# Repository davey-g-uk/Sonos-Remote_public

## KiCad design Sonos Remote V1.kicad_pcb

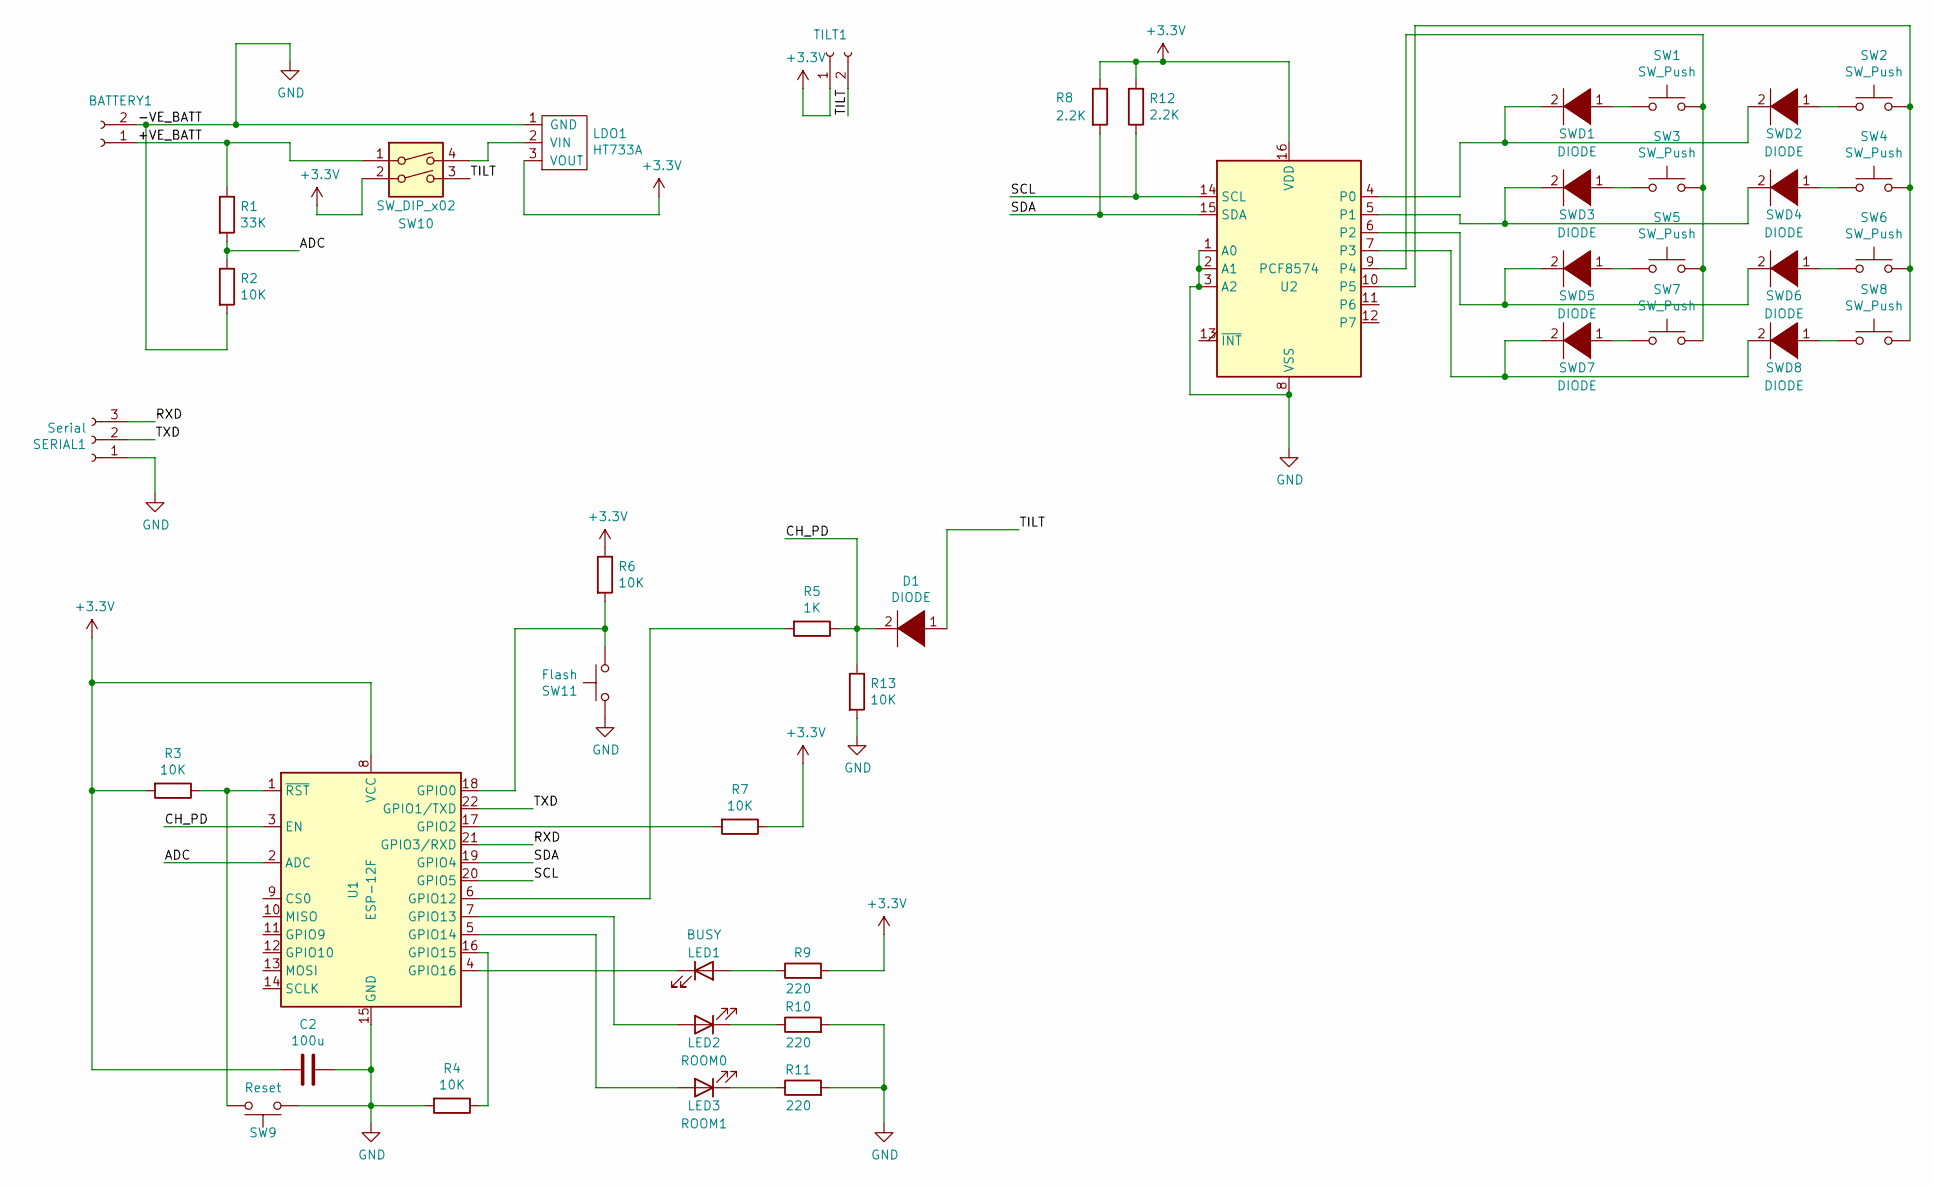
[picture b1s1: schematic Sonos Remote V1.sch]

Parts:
BATTERY1: Conn_01x02_Female; PinHeader_1x02_P2.00mm_Vertical
C2: 100u; C_Radial_D5.0mm_H11.0mm_P2.00mm
D1: DIODE; D_T-1_P5.08mm_Horizontal
LDO1: HT733A
LED1: BUSY; LED_D3.0mm
LED2: ROOM0; LED_D3.0mm
LED3: ROOM1; LED_D3.0mm
R1: 33K; R_Axial_DIN0207_L6.3mm_D2.5mm_P7.62mm_Horizontal
R2, R3, R4, R6, R7, R13: 10K; R_Axial_DIN0207_L6.3mm_D2.5mm_P7.62mm_Horizontal
R5: 1K; R_Axial_DIN0207_L6.3mm_D2.5mm_P7.62mm_Horizontal
R8, R12: 2.2K; R_Axial_DIN0207_L6.3mm_D2.5mm_P7.62mm_Horizontal
R9, R10, R11: 220; R_Axial_DIN0207_L6.3mm_D2.5mm_P7.62mm_Horizontal
SERIAL1: Serial; PinHeader_1x03_P2.00mm_Vertical
SW1, SW2, SW3, SW4, SW5, SW6, SW7, SW8: SW_Push; SW_Cherry_MX_1.00u_PCB
SW9: Reset; SW_PUSH_6mm
SW10: SW_DIP_x02; SW_DIP_SPSTx02_Slide_6.7x6.64mm_W7.62mm_P2.54mm_LowProfile
SW11: Flash; SW_PUSH_6mm
SWD1, SWD2, SWD3, SWD4, SWD5, SWD6, SWD7, SWD8: DIODE; D_T-1_P5.08mm_Horizontal
TILT1: Conn_01x02_Female; PinHeader_1x02_P2.00mm_Vertical
U1: ESP-12F; ESP-12E
U2: PCF8574; SOIC-16W_7.5x10.3mm_P1.27mm

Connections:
+3V3: C2.2, LDO1.3 (VOUT), R3.2, R6.1, R7.1, R8.1, R9.2, R12.2, SW10.2, TILT1.1, U1.8 (VCC), U2.16 (VDD); also elsewhere on the board
/+VE_BATT: BATTERY1.1, R1.1, SW10.1; also elsewhere on the board
/ADC: R1.2, R2.1, U1.2 (ADC)
/CH_PD: D1.2 (A), R5.1, R13.1, U1.3 (EN)
/RXD: SERIAL1.3, U1.21 (GPIO3/RXD); also elsewhere on the board
/SCL: R12.1, U1.20 (GPIO5), U2.14 (SCL)
/SDA: R8.2, U1.19 (GPIO4), U2.15 (SDA)
/TILT: D1.1 (K), SW10.3, TILT1.2; also elsewhere on the board
/TXD: SERIAL1.2, U1.22 (GPIO1/TXD); also elsewhere on the board
GND: BATTERY1.2, C2.1, LDO1.1 (GND), R2.2, R4.2, R10.2, R11.2, R13.2, SERIAL1.1, SW9.1, SW11.1, U1.15 (GND), U2.1 (A0), U2.2 (A1), U2.3 (A2), U2.8 (VSS); also elsewhere on the board
unnamed: LDO1.2 (VIN), SW10.4
unnamed: LED1.1 (K), U1.4 (GPIO16)
unnamed: LED1.2 (A), R9.1
unnamed: LED2.1 (K), R10.1
unnamed: LED2.2 (A), U1.7 (GPIO13)
unnamed: LED3.1 (K), R11.1
unnamed: LED3.2 (A), U1.5 (GPIO14)
unnamed: R3.1, SW9.2, U1.1 (~RST)
unnamed: R4.1, U1.16 (GPIO15)
unnamed: R5.2, U1.6 (GPIO12)
unnamed: R6.2, SW11.2, U1.18 (GPIO0)
unnamed: R7.2, U1.17 (GPIO2)
unnamed: SW1.1, SWD1.1 (K)
unnamed: SW1.2, SW3.2, SW5.2, SW7.2, U2.9 (P4)
unnamed: SW2.1, SWD2.1 (K)
unnamed: SW2.2, SW4.2, SW6.2, SW8.2, U2.10 (P5)
unnamed: SW3.1, SWD3.1 (K)
unnamed: SW4.1, SWD4.1 (K)
unnamed: SW5.1, SWD5.1 (K)
unnamed: SW6.1, SWD6.1 (K)
unnamed: SW7.1, SWD7.1 (K)
unnamed: SW8.1, SWD8.1 (K)
unnamed: SWD1.2 (A), SWD2.2 (A), U2.4 (P0)
unnamed: SWD3.2 (A), SWD4.2 (A), U2.5 (P1)
unnamed: SWD5.2 (A), SWD6.2 (A), U2.6 (P2)
unnamed: SWD7.2 (A), SWD8.2 (A), U2.7 (P3)

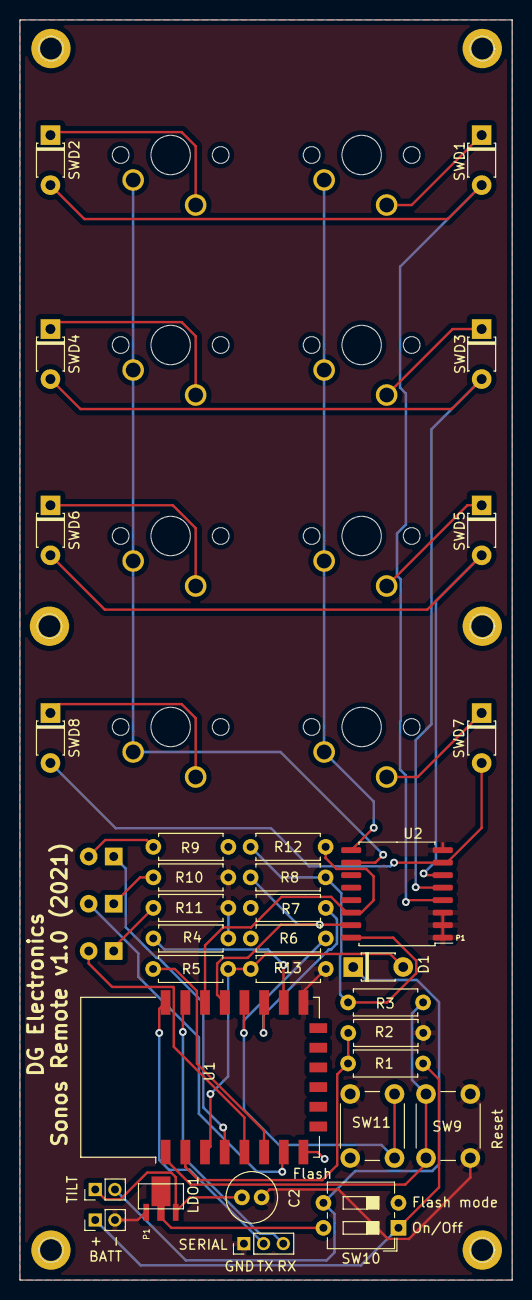
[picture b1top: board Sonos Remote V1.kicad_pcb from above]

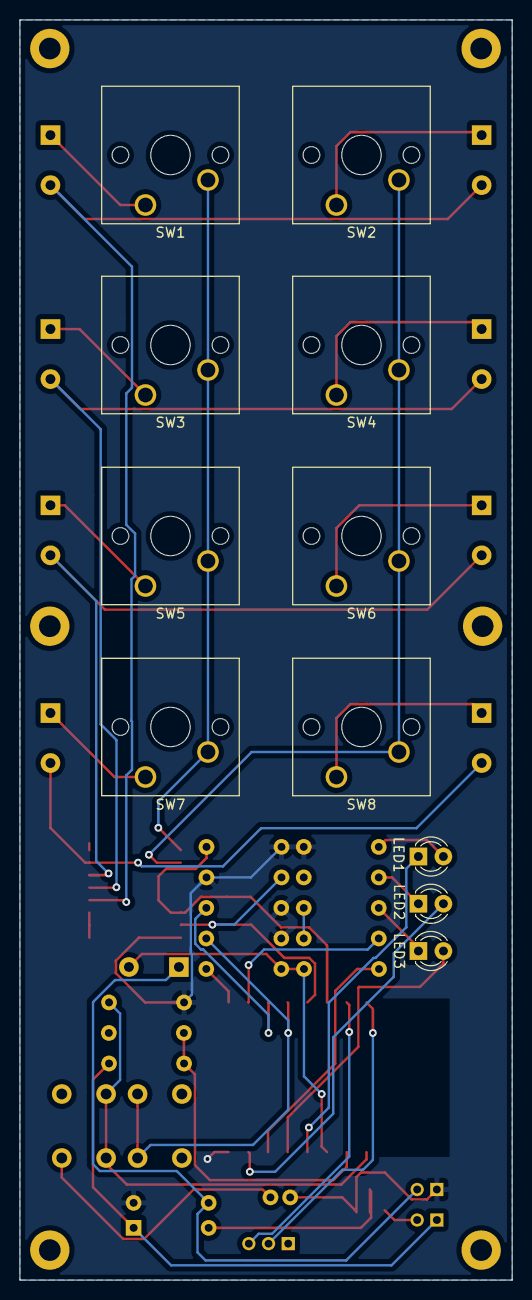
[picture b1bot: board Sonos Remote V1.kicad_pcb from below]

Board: 2 copper layers, 50.0 x 128.0 mm, 49 parts (11 on the bottom side), 36 nets.

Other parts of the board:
 : Pin_D1.0mm_L10.0mm
 #2,  #3,  #4,  #5,  #6: Pin_D1.0mm_L10.0mm
BATT: Conn_01x02_Female; PinHeader_1x02_P2.00mm_Vertical
SERIAL: Serial; PinHeader_1x03_P2.00mm_Vertical
TILT: Conn_01x02_Female; PinHeader_1x02_P2.00mm_Vertical

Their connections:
+3V3: TILT.1; also elsewhere on the board
/+VE_BATT: BATT.1; also elsewhere on the board
/RXD: SERIAL.3; also elsewhere on the board
/TILT: TILT.2; also elsewhere on the board
/TXD: SERIAL.2; also elsewhere on the board
GND: BATT.2, SERIAL.1; also elsewhere on the board

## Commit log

2021-04-23 Version 1 Schematics & PCB
2021-04-23 Added files (pdf)
2021-04-23 added PCB PDF
